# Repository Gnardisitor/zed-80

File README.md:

# zed-80
Simple Z80 computer based on Grant Searle's Z80 computer.

### Board

The first iteration of the board had an issue with the clock circuit since I used a 74LS04, which is a non-CMOS IC. The modified Pierce oscillator circuit I made does not function with non-CMOS inverters.

With a modified resistor configuration and a 74HCT04 inverter, I did manage to get a stable clock. However, the UART IC never let the CTS pin to low, therefore never sending any data. Without a logic analyzer, I am unable to check whether the IC, circuit, or the assembly code is bad.

Another issue with my attempt to make this board very quickly is that I based my design almost completely on Grant Searle's Z80 design and used his ported code directly, which gives me less room for making my own changes. For the next version I will base it more on my own design and try the modular ROMWBW firmware instead, which should give me more chances to modify it for my own needs.

### Programmer

The programmer is based on the TommyPROM project, but I turned it into an Arduino Uno shield, which makes it more compact and easy to use. However, my version is limited to flashing only the AT28C256, which makes it much less useful for other projects. For future endeavors, I will most likely buy an XGecu T48 programmer to remove extra points of failure.

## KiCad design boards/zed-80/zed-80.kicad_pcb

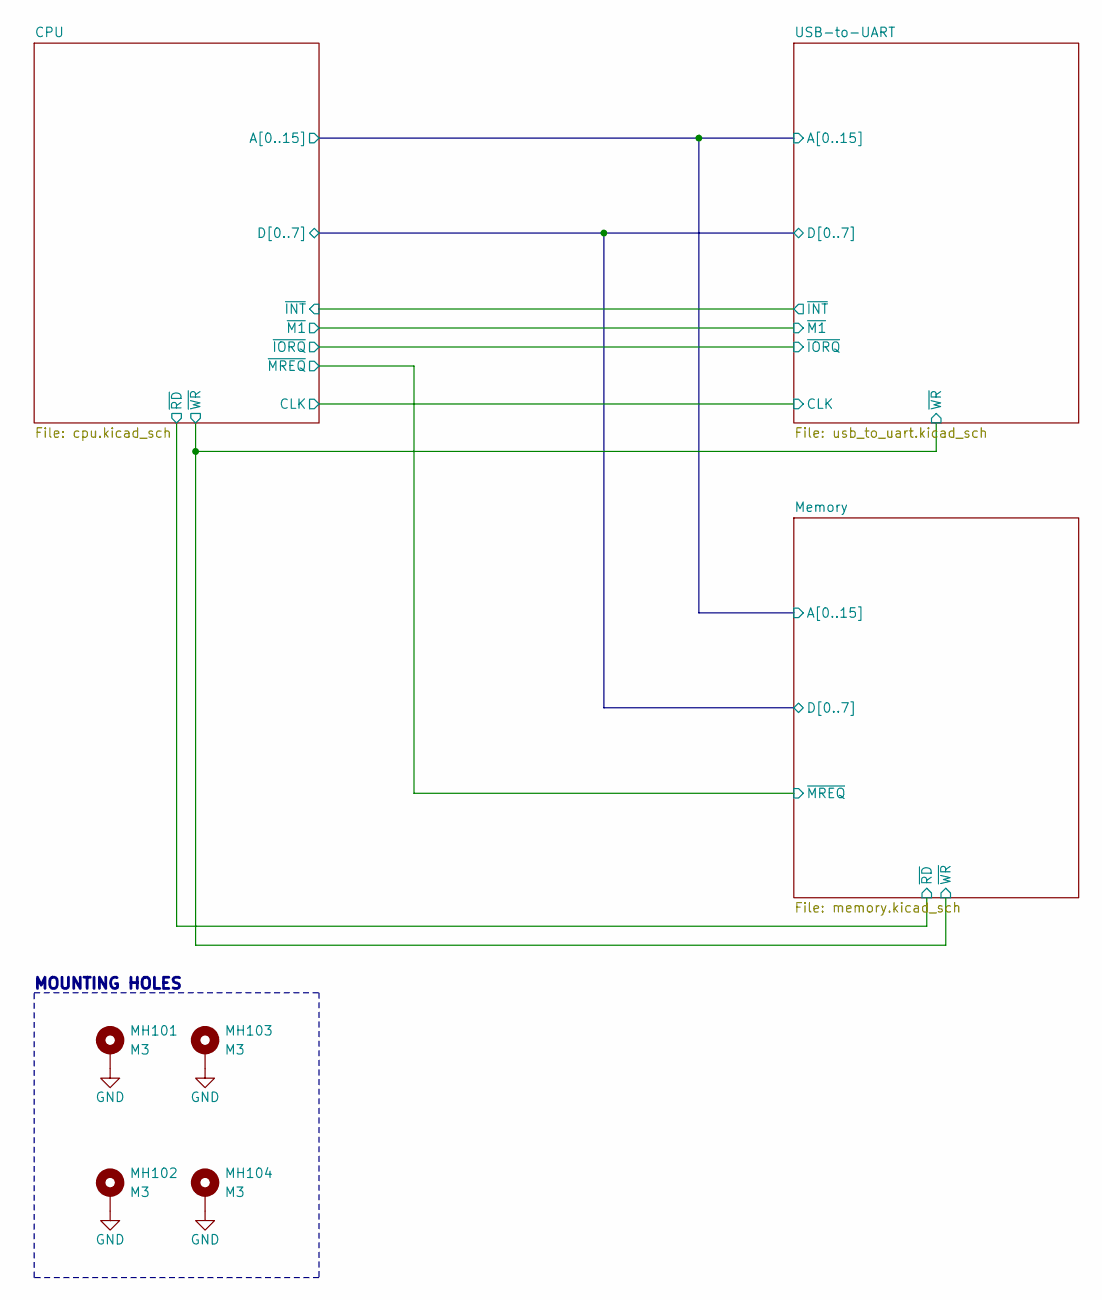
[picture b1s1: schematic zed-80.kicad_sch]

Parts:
MH101, MH102, MH103, MH104: M3; MountingHole_3.2mm_M3_Pad_Via

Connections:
GND: MH101.1, MH102.1, MH103.1, MH104.1; also elsewhere on the board

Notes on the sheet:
MOUNTING HOLES

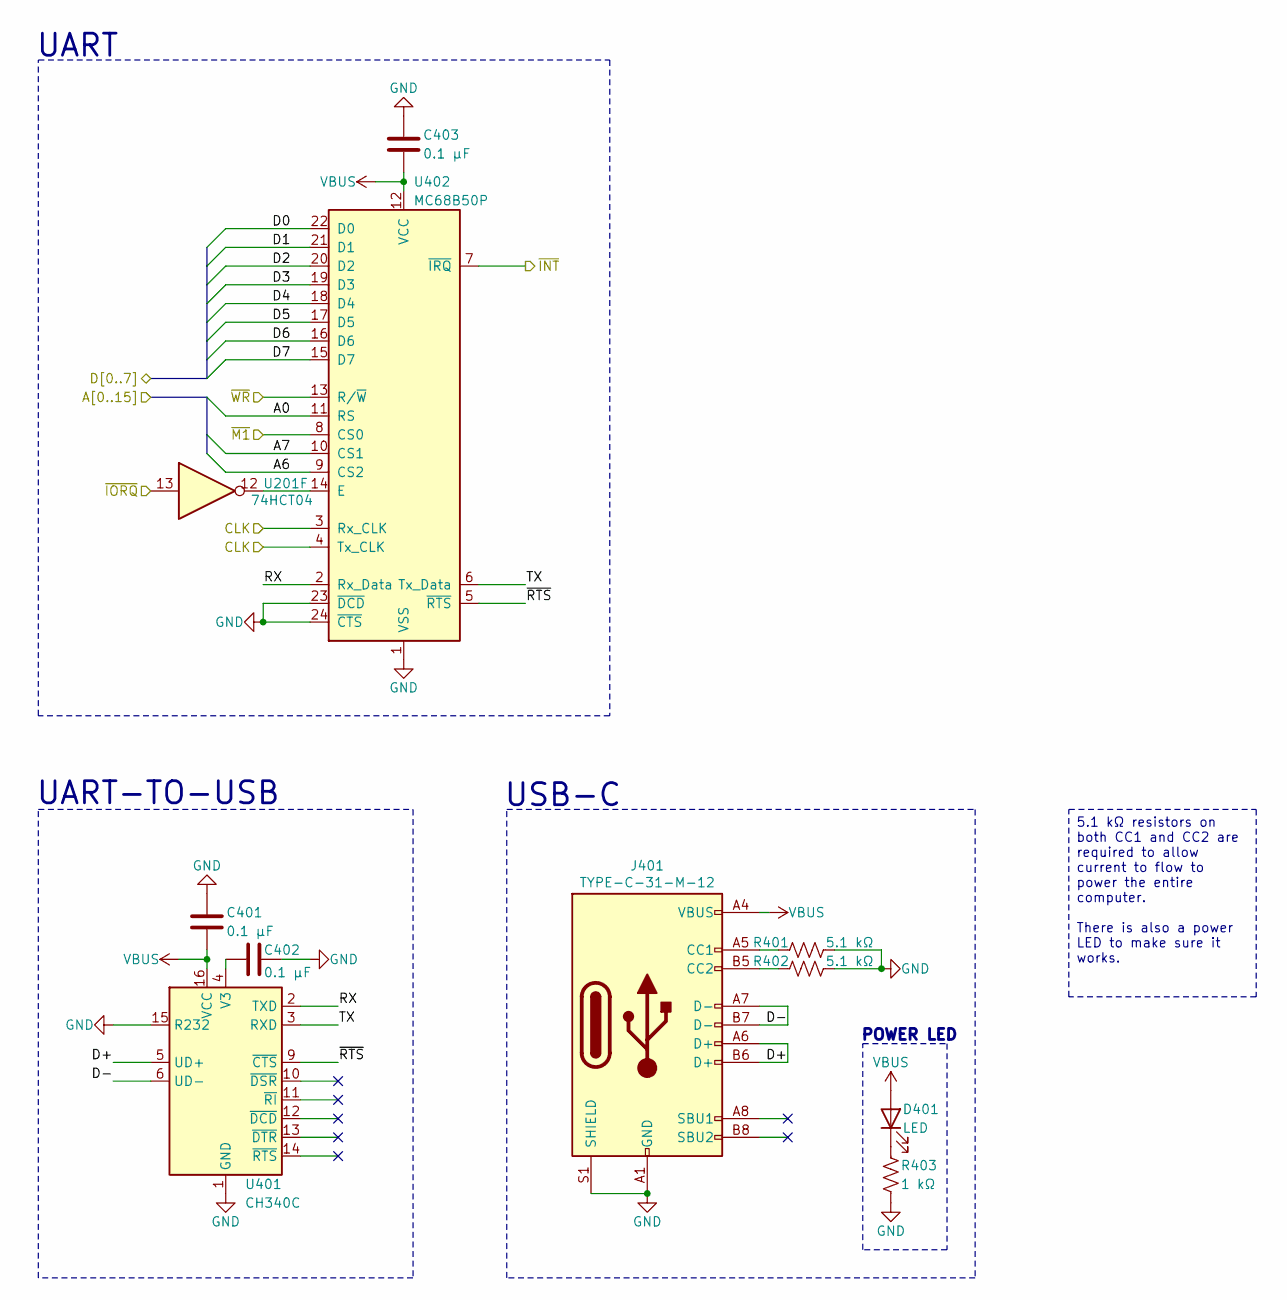
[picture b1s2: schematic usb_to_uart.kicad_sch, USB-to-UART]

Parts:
C401, C402, C403: 0.1 µF; C_Disc_D5.0mm_W2.5mm_P5.00mm
D401: LED; LED_D5.0mm
J401: TYPE-C-31-M-12; USB_C_Receptacle_HRO_TYPE-C-31-M-12
R401, R402: 5.1 kΩ; R_Axial_DIN0207_L6.3mm_D2.5mm_P7.62mm_Horizontal
R403: 1 kΩ; R_Axial_DIN0207_L6.3mm_D2.5mm_P7.62mm_Horizontal
U201: 74HCT04; DIP-14_W7.62mm_Socket_LongPads
U401: CH340C; SOIC-16_3.9x9.9mm_P1.27mm
U402: MC68B50P; DIP-24_W15.24mm_Socket_LongPads

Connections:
/CPU/A0: U402.11 (RS); also elsewhere on the board
/CPU/A6: U402.9 (CS2); also elsewhere on the board
/CPU/A7: U402.10 (CS1); also elsewhere on the board
/CPU/CLK: U402.3 (Rx_CLK), U402.4 (Tx_CLK); also elsewhere on the board
/CPU/D0: U402.22 (D0); also elsewhere on the board
/CPU/D1: U402.21 (D1); also elsewhere on the board
/CPU/D2: U402.20 (D2); also elsewhere on the board
/CPU/D3: U402.19 (D3); also elsewhere on the board
/CPU/D4: U402.18 (D4); also elsewhere on the board
/CPU/D5: U402.17 (D5); also elsewhere on the board
/CPU/D6: U402.16 (D6); also elsewhere on the board
/CPU/D7: U402.15 (D7); also elsewhere on the board
/CPU/~INT: U402.7 (~IRQ); also elsewhere on the board
/CPU/~IORQ: U201.13; also elsewhere on the board
/CPU/~M1: U402.8 (CS0); also elsewhere on the board
/CPU/~WR: U402.13 (R/~W); also elsewhere on the board
/USB-to-UART/D+: J401.A6 (D+), J401.B6 (D+), U401.5 (UD+)
/USB-to-UART/D-: J401.A7 (D-), J401.B7 (D-), U401.6 (UD-)
/USB-to-UART/RX: U401.2 (TXD), U402.2 (Rx_Data)
/USB-to-UART/TX: U401.3 (RXD), U402.6 (Tx_Data)
/USB-to-UART/~RTS: U401.9 (~CTS), U402.5 (~RTS)
GND: C401.1, C402.2, C403.1, J401.A1 (GND), J401.A12 (GND), J401.B1 (GND), J401.B12 (GND), J401.S1 (SHIELD), R401.2, R402.2, R403.2, U401.1 (GND), U401.15 (R232), U402.1 (VSS), U402.23 (~DCD), U402.24 (~CTS); also elsewhere on the board
unnamed: D401.1 (K), R403.1
unnamed: J401.A5 (CC1), R401.1
unnamed: J401.B5 (CC2), R402.1
unnamed: C402.1, U401.4 (V3)
unnamed: U201.12, U402.14 (E)
VBUS: C401.2, C403.2, D401.2 (A), J401.A4 (VBUS), J401.A9 (VBUS), J401.B4 (VBUS), J401.B9 (VBUS), U401.16 (VCC), U402.12 (VCC); also elsewhere on the board

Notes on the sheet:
UART-TO-USB
UART
POWER LED
USB-C
5.1 kΩ resistors on both CC1 and CC2 are required to allow current to flow to power the entire computer. There is also a power LED to make sure it works.

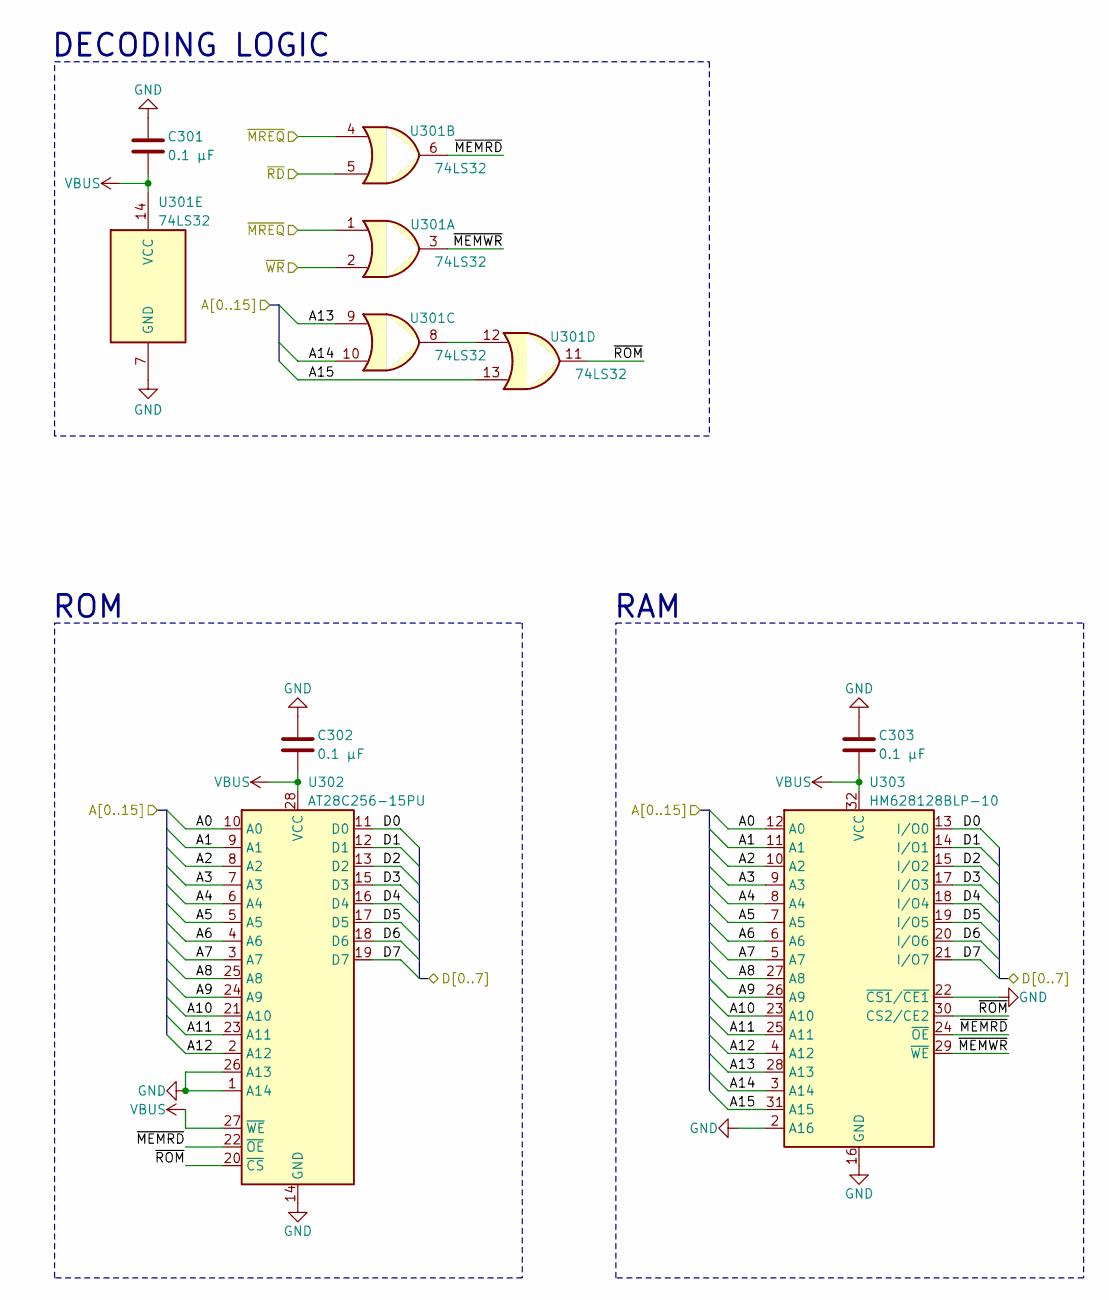
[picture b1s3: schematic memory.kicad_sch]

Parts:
C301, C302, C303: 0.1 µF; C_Disc_D5.0mm_W2.5mm_P5.00mm
U301: 74LS32; DIP-14_W7.62mm_Socket_LongPads
U302: AT28C256-15PU; DIP-28_W15.24mm_Socket_LongPads
U303: HM628128BLP-10; DIP-32_W15.24mm_Socket_LongPads

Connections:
/CPU/A0: U302.10 (A0), U303.12 (A0); also elsewhere on the board
/CPU/A1: U302.9 (A1), U303.11 (A1); also elsewhere on the board
/CPU/A2: U302.8 (A2), U303.10 (A2); also elsewhere on the board
/CPU/A3: U302.7 (A3), U303.9 (A3); also elsewhere on the board
/CPU/A4: U302.6 (A4), U303.8 (A4); also elsewhere on the board
/CPU/A5: U302.5 (A5), U303.7 (A5); also elsewhere on the board
/CPU/A6: U302.4 (A6), U303.6 (A6); also elsewhere on the board
/CPU/A7: U302.3 (A7), U303.5 (A7); also elsewhere on the board
/CPU/A8: U302.25 (A8), U303.27 (A8); also elsewhere on the board
/CPU/A9: U302.24 (A9), U303.26 (A9); also elsewhere on the board
/CPU/A10: U302.21 (A10), U303.23 (A10); also elsewhere on the board
/CPU/A11: U302.23 (A11), U303.25 (A11); also elsewhere on the board
/CPU/A12: U302.2 (A12), U303.4 (A12); also elsewhere on the board
/CPU/A13: U301.9, U303.28 (A13); also elsewhere on the board
/CPU/A14: U301.10, U303.3 (A14); also elsewhere on the board
/CPU/A15: U301.13, U303.31 (A15); also elsewhere on the board
/CPU/D0: U302.11 (D0), U303.13 (I/O0); also elsewhere on the board
/CPU/D1: U302.12 (D1), U303.14 (I/O1); also elsewhere on the board
/CPU/D2: U302.13 (D2), U303.15 (I/O2); also elsewhere on the board
/CPU/D3: U302.15 (D3), U303.17 (I/O3); also elsewhere on the board
/CPU/D4: U302.16 (D4), U303.18 (I/O4); also elsewhere on the board
/CPU/D5: U302.17 (D5), U303.19 (I/O5); also elsewhere on the board
/CPU/D6: U302.18 (D6), U303.20 (I/O6); also elsewhere on the board
/CPU/D7: U302.19 (D7), U303.21 (I/O7); also elsewhere on the board
/CPU/~MREQ: U301.1, U301.4; also elsewhere on the board
/CPU/~RD: U301.5; also elsewhere on the board
/CPU/~WR: U301.2; also elsewhere on the board
/Memory/~MEMRD: U301.6, U302.22 (~OE), U303.24 (~OE)
/Memory/~MEMWR: U301.3, U303.29 (~WE)
/Memory/~ROM: U301.11, U302.20 (~CS), U303.30 (CS2/CE2)
GND: C301.1, C302.1, C303.1, U301.7 (GND), U302.1 (A14), U302.14 (GND), U302.26 (A13), U303.2 (A16), U303.16 (GND), U303.22 (~CS1/~CE1); also elsewhere on the board
unnamed: U301.8, U301.12
VBUS: C301.2, C302.2, C303.2, U301.14 (VCC), U302.27 (~WE), U302.28 (VCC), U303.32 (VCC); also elsewhere on the board

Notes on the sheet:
RAM
ROM
DECODING LOGIC

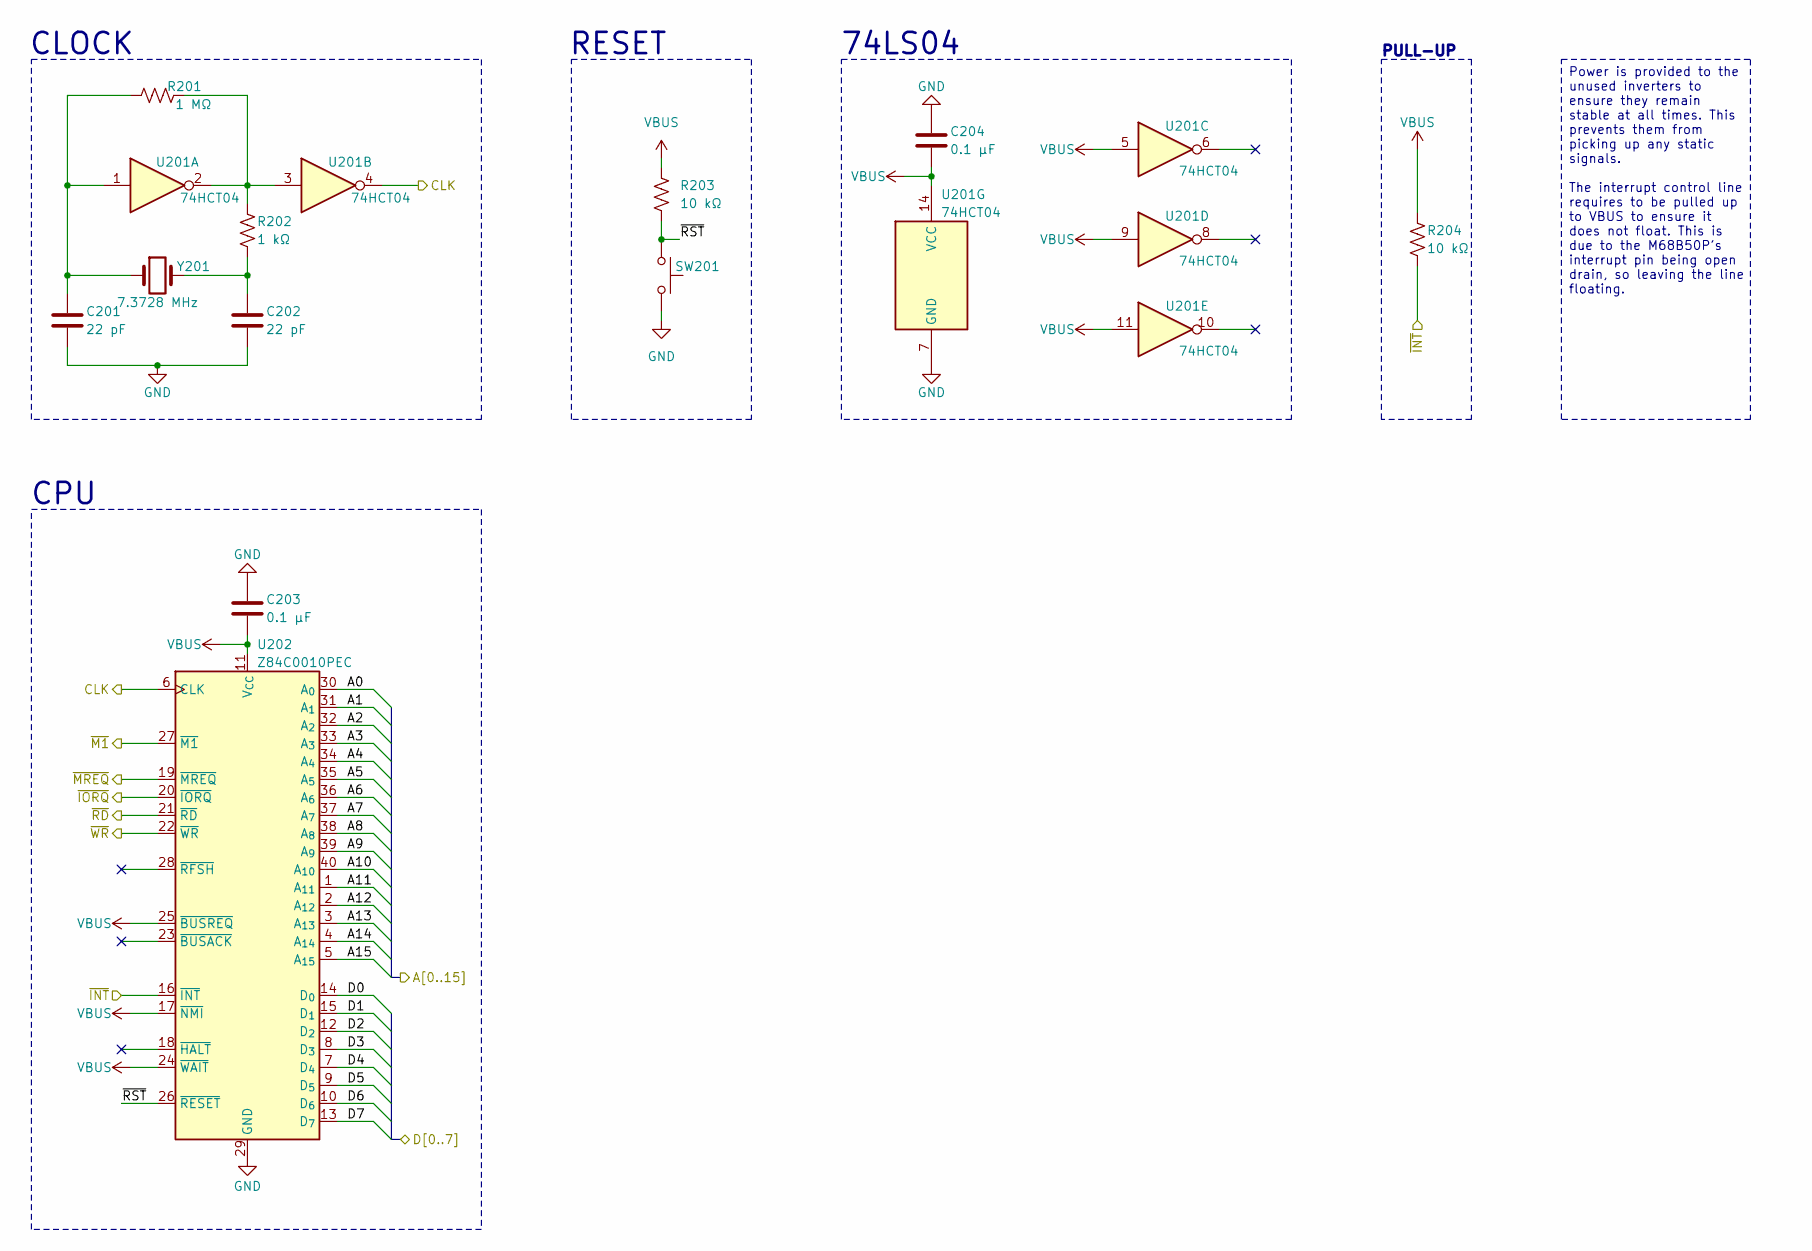
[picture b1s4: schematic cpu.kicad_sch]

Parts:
C201, C202: 22 pF; C_Disc_D5.0mm_W2.5mm_P5.00mm
C203, C204: 0.1 µF; C_Disc_D5.0mm_W2.5mm_P5.00mm
R201: 1 MΩ; R_Axial_DIN0207_L6.3mm_D2.5mm_P7.62mm_Horizontal
R202: 1 kΩ; R_Axial_DIN0207_L6.3mm_D2.5mm_P7.62mm_Horizontal
R203, R204: 10 kΩ; R_Axial_DIN0207_L6.3mm_D2.5mm_P7.62mm_Horizontal
SW201: SW_Push; SW_PUSH_6mm
U201: 74HCT04; DIP-14_W7.62mm_Socket_LongPads
U202: Z84C0010PEC; DIP-40_W15.24mm_Socket_LongPads
Y201: 7.3728 MHz; Crystal_HC49-4H_Vertical

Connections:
/CPU/A0: U202.30 (A_{0}); also elsewhere on the board
/CPU/A1: U202.31 (A_{1}); also elsewhere on the board
/CPU/A2: U202.32 (A_{2}); also elsewhere on the board
/CPU/A3: U202.33 (A_{3}); also elsewhere on the board
/CPU/A4: U202.34 (A_{4}); also elsewhere on the board
/CPU/A5: U202.35 (A_{5}); also elsewhere on the board
/CPU/A6: U202.36 (A_{6}); also elsewhere on the board
/CPU/A7: U202.37 (A_{7}); also elsewhere on the board
/CPU/A8: U202.38 (A_{8}); also elsewhere on the board
/CPU/A9: U202.39 (A_{9}); also elsewhere on the board
/CPU/A10: U202.40 (A_{10}); also elsewhere on the board
/CPU/A11: U202.1 (A_{11}); also elsewhere on the board
/CPU/A12: U202.2 (A_{12}); also elsewhere on the board
/CPU/A13: U202.3 (A_{13}); also elsewhere on the board
/CPU/A14: U202.4 (A_{14}); also elsewhere on the board
/CPU/A15: U202.5 (A_{15}); also elsewhere on the board
/CPU/CLK: U201.4, U202.6 (CLK); also elsewhere on the board
/CPU/D0: U202.14 (D_{0}); also elsewhere on the board
/CPU/D1: U202.15 (D_{1}); also elsewhere on the board
/CPU/D2: U202.12 (D_{2}); also elsewhere on the board
/CPU/D3: U202.8 (D_{3}); also elsewhere on the board
/CPU/D4: U202.7 (D_{4}); also elsewhere on the board
/CPU/D5: U202.9 (D_{5}); also elsewhere on the board
/CPU/D6: U202.10 (D_{6}); also elsewhere on the board
/CPU/D7: U202.13 (D_{7}); also elsewhere on the board
/CPU/~INT: R204.2, U202.16 (~INT); also elsewhere on the board
/CPU/~IORQ: U202.20 (~IORQ); also elsewhere on the board
/CPU/~M1: U202.27 (~M1); also elsewhere on the board
/CPU/~MREQ: U202.19 (~MREQ); also elsewhere on the board
/CPU/~RD: U202.21 (~RD); also elsewhere on the board
/CPU/~RST: R203.2, SW201.1, U202.26 (~RESET)
/CPU/~WR: U202.22 (~WR); also elsewhere on the board
GND: C201.2, C202.2, C203.1, C204.1, SW201.2, U201.7 (GND), U202.29 (GND); also elsewhere on the board
unnamed: C201.1, R201.1, U201.1, Y201.1
unnamed: C202.1, R202.2, Y201.2
unnamed: R201.2, R202.1, U201.2, U201.3
VBUS: C203.2, C204.2, R203.1, R204.1, U201.5, U201.9, U201.11, U201.14 (VCC), U202.11 (V_{CC}), U202.17 (~NMI), U202.24 (~WAIT), U202.25 (~BUSREQ); also elsewhere on the board

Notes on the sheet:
74LS04
CLOCK
CPU
PULL-UP
RESET
Power is provided to the unused inverters to ensure they remain stable at all times. This prevents them from picking up any static signals. The interrupt control line requires to be pulled up to VBUS to ensure it does not float. This is due to the M68B50P's interrupt pin being open drain, so leavin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

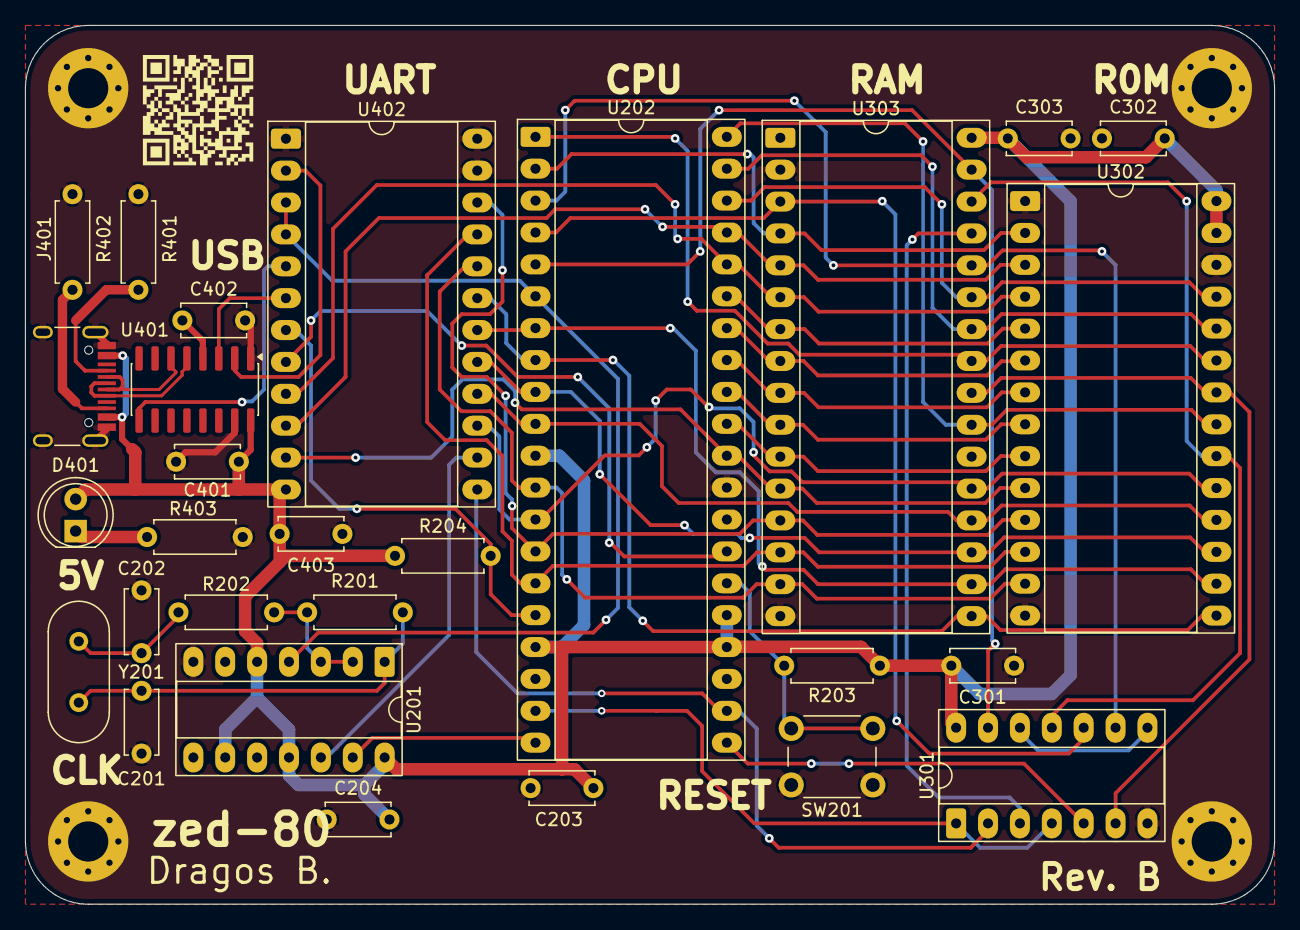
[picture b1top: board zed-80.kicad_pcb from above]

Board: 2 copper layers, 99.5 x 70.0 mm, 32 parts (0 on the bottom side), 51 nets.

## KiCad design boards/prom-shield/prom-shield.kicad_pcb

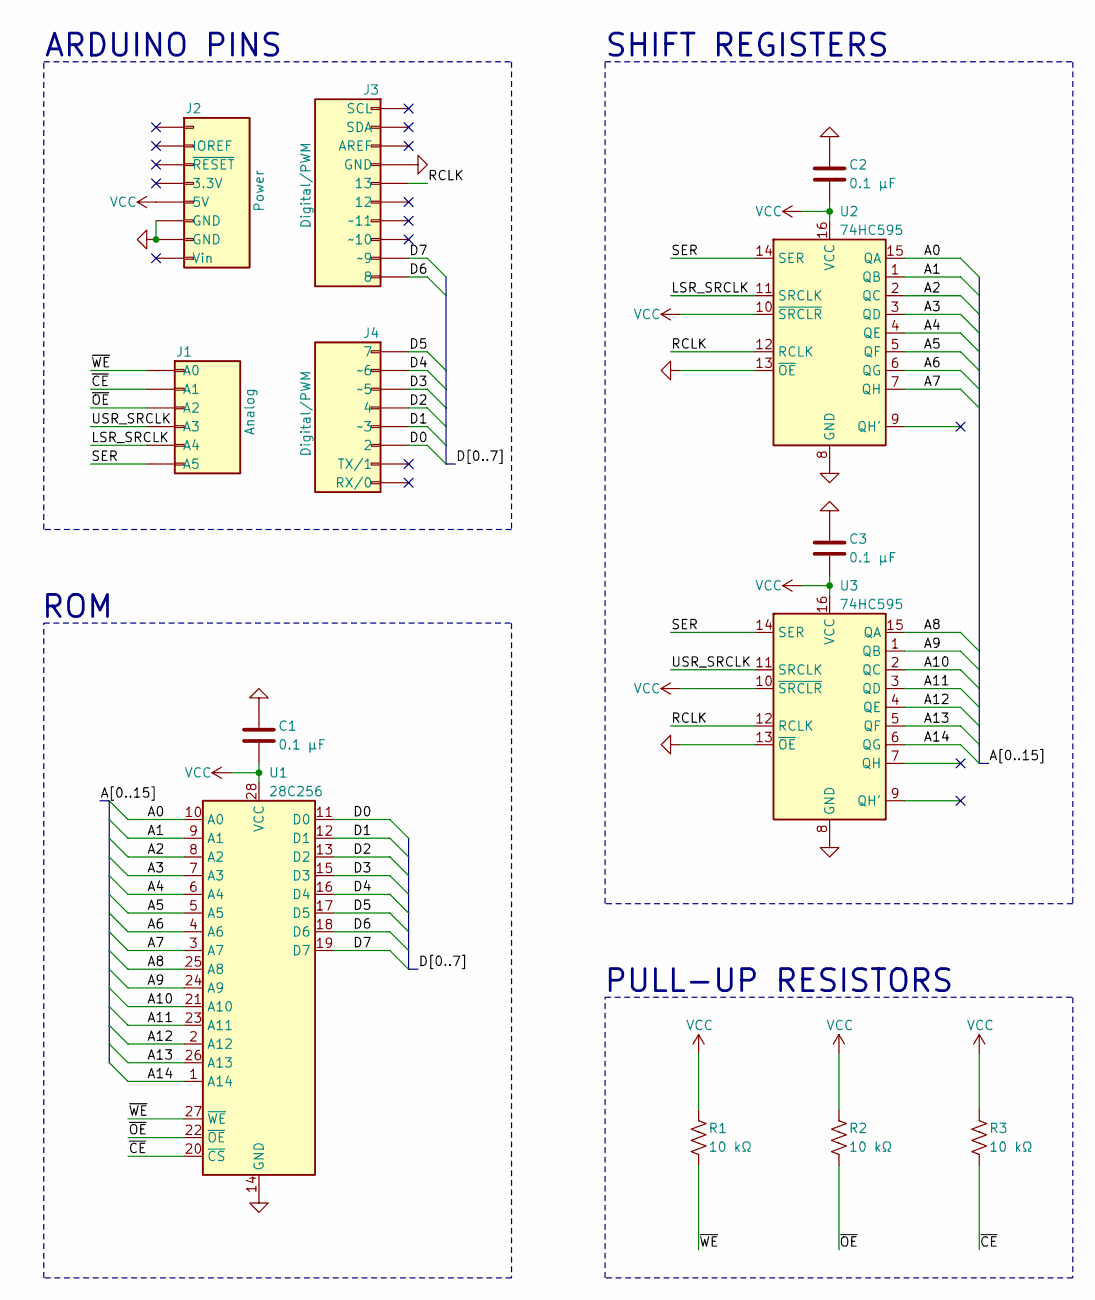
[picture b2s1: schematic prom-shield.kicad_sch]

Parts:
C1, C2, C3: 0.1 µF; C_Disc_D5.0mm_W2.5mm_P5.00mm
J1: Analog; PinSocket_1x06_P2.54mm_Vertical
J2: Power; PinSocket_1x08_P2.54mm_Vertical
J3: Digital/PWM; PinSocket_1x10_P2.54mm_Vertical
J4: Digital/PWM; PinSocket_1x08_P2.54mm_Vertical
R1, R2, R3: 10 kΩ; R_Axial_DIN0207_L6.3mm_D2.5mm_P7.62mm_Horizontal
U1: 28C256; DIP_Socket-28_W11.9mm_W12.7mm_W15.24mm_W17.78mm_W18.5mm_3M_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
U2, U3: 74HC595; DIP-16_W7.62mm_Socket_LongPads

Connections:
/A0: U1.10 (A0), U2.15 (QA)
/A1: U1.9 (A1), U2.1 (QB)
/A2: U1.8 (A2), U2.2 (QC)
/A3: U1.7 (A3), U2.3 (QD)
/A4: U1.6 (A4), U2.4 (QE)
/A5: U1.5 (A5), U2.5 (QF)
/A6: U1.4 (A6), U2.6 (QG)
/A7: U1.3 (A7), U2.7 (QH)
/A8: U1.25 (A8), U3.15 (QA)
/A9: U1.24 (A9), U3.1 (QB)
/A10: U1.21 (A10), U3.2 (QC)
/A11: U1.23 (A11), U3.3 (QD)
/A12: U1.2 (A12), U3.4 (QE)
/A13: U1.26 (A13), U3.5 (QF)
/A14: U1.1 (A14), U3.6 (QG)
/D0: J4.6 (2), U1.11 (D0)
/D1: J4.5 (~3), U1.12 (D1)
/D2: J4.4, U1.13 (D2)
/D3: J4.3 (~5), U1.15 (D3)
/D4: J4.2 (~6), U1.16 (D4)
/D5: J4.1 (7), U1.17 (D5)
/D6: J3.10 (8), U1.18 (D6)
/D7: J3.9 (~9), U1.19 (D7)
/LSR_SRCLK: J1.5 (A4), U2.11 (SRCLK)
/RCLK: J3.5 (13), U2.12 (RCLK), U3.12 (RCLK)
/SER: J1.6 (A5), U2.14 (SER), U3.14 (SER)
/USR_SRCLK: J1.4 (A3), U3.11 (SRCLK)
/~CE: J1.2 (A1), R3.2, U1.20 (~CS)
/~OE: J1.3 (A2), R2.2, U1.22 (~OE)
/~WE: J1.1 (A0), R1.2, U1.27 (~WE)
GND: C1.1, C2.1, C3.1, J2.6 (GND), J2.7 (GND), J3.4 (GND), U1.14 (GND), U2.8 (GND), U2.13 (~OE), U3.8 (GND), U3.13 (~OE)
VCC: C1.2, C2.2, C3.2, J2.5 (5V), R1.1, R2.1, R3.1, U1.28 (VCC), U2.10 (~SRCLR), U2.16 (VCC), U3.10 (~SRCLR), U3.16 (VCC)

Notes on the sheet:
PULL-UP RESISTORS
SHIFT REGISTERS
ROM
ARDUINO PINS

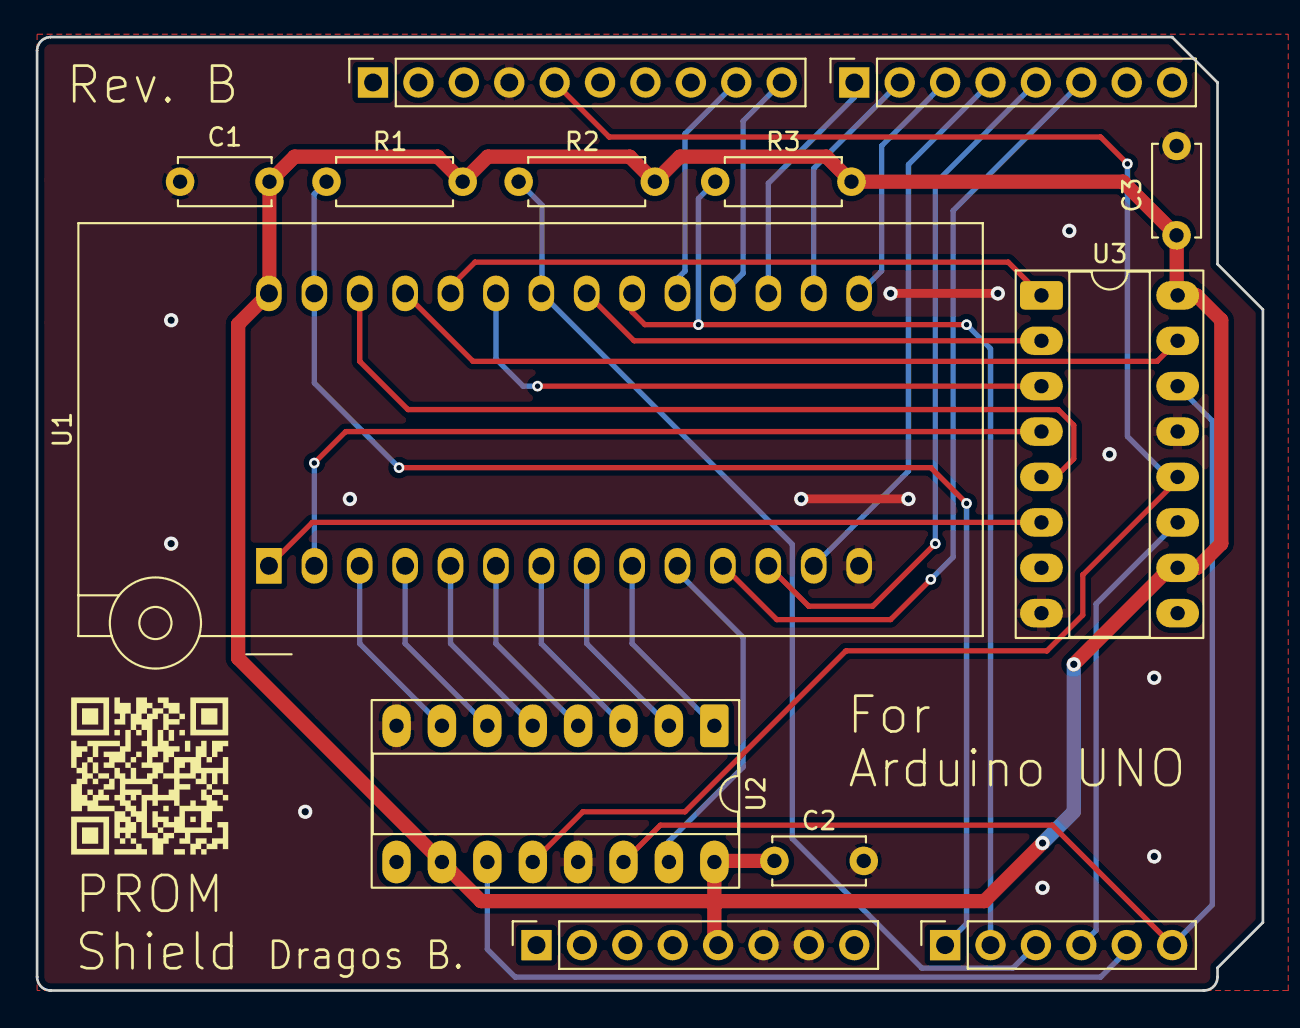
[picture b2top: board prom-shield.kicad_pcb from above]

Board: 2 copper layers, 68.6 x 53.3 mm, 13 parts (0 on the bottom side), 32 nets.

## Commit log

2025-12-22 Added .gitignore file
2025-12-22 Created Altium project
2025-12-22 Created component symbols and footprints
2025-12-22 Initial Z80 schematics
2025-12-23 Finalized first revision of Z80 schematics
2025-12-30 Slight changes to footprints and initial footprint generation for components on PCB
2025-12-31 Created initial KiCAD schematics
2025-12-31 Polished schematics and basic PCB setup
2025-12-31 Fixed .gitignore for both Altium and KiCAD
2026-01-02 New zed-80 revision and initial ROM programmer schematic
2026-01-02 Initial PCB revision for ROM programmer
2026-01-02 Small tweaks and new schematics PDF
2026-01-02 Small routing tweaks to ROM programmer PCB
2026-02-13 Initial layout for main board
2026-02-14 Initial PCB design for main board
2026-02-14 Fixed DRC errors and added silkscreens
2026-02-15 Fixed small issues and added QR code to main board
2026-02-15 Small fixup of main board
2026-02-15 New revision of PROM board
2026-02-15 Fixed QR code library linking
2026-02-15 Small cleanup for PROM board
2026-02-15 Removed unused Altium version from main branch
2026-02-15 Shortened main board
2026-02-15 Cleanup main board
2026-02-15 Embedded font files
2026-02-16 Final touchups and produced fabrication files
2026-03-18 Fixed clock oscillator circuit
2026-03-20 Small tweaks
2026-03-21 Updated to KiCAD 10
